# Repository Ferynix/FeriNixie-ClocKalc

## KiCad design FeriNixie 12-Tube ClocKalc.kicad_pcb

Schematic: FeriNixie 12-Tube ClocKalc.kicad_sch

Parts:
C1, C2, C3, C4, C5, C6, C7, C8, C9, C10, C11, C12, C51, C52: 100nF; C_1206_3216Metric; JLCPCB_PN C725802
C13, C14, C15, C16, C17, C18, C19, C20, C21, C22, C23, C24, C25, C26, C27, C28, C29, C30, C36: 1uF; C_0402_1005Metric; JLCPCB_PN C725802
C31, C32, C35, C37, C45, C46: 4.7uF; C_0402_1005Metric; JLCPCB_PN C725802
C33, C34: 15pF; C_0402_1005Metric; JLCPCB_PN C725802
C38, C39, C40, C41, C42, C43, C44, C47, C48: 100nF; C_0402_1005Metric; JLCPCB_PN C725802
D1: SMCJ150CA_C41411757; SMC_L6.9-W5.9-LS7.9-BI; LCSC C41411757
F1: C354900; C_Disc_D10.5mm_W5.0mm_P5.00mm; not fitted
J1: Conn_01x02_Socket; PinSocket_1x02_P1.00mm_Vertical
NE1: Run; NeonIndicator_A1B_A1C
NE2: NeonIndicator_2ML_1MH_B10A
NE3: Voltage Indicator; NeonIndicator_2ML_1MH_B10A
NE4: BLOWN; NeonIndicator_A1B_A1C
NX1, NX2, NX3, NX4, NX5, NX6, NX7, NX8, NX9, NX10, NX11, NX12: NixieTube_B-16851453_Burroughs
Q1, Q2, Q3, Q4, Q5, Q6, Q7, Q8, Q9, Q10, Q11, Q12, Q13, Q14, Q15, Q16, Q17, Q18, Q19, Q20, Q21, Q22, Q23, Q24, Q25, Q26, Q27, Q28, Q29, Q30, Q31, Q32, Q33, Q34, Q35, Q36, Q37, Q38, Q39, Q40, Q41, Q42, Q43, Q44, Q45, Q46, Q47, Q48, Q49, Q50, Q51, Q52, Q53, Q54, Q55, Q56, Q57, Q58, Q59, Q60, Q61, Q62, Q63, Q64, Q65, Q66, Q67, Q68, Q69, Q70, Q71, Q72, Q73, Q74, Q75, Q76, Q77, Q78, Q79, Q80, Q81, Q82, Q83, Q84, Q85, Q86, Q87, Q88, Q89, Q90, Q91, Q92, Q93, Q94, Q95, Q96, Q97, Q98, Q99, Q100, Q101, Q102, Q103, Q104, Q105, Q106, Q107, Q108, Q109, Q110, Q111, Q112, Q113, Q114, Q115, Q116, Q117, Q118, Q119, Q120, Q121, Q122, Q123, Q124, Q125, Q126, Q127, Q128, Q129, Q130, Q131, Q132, Q133, Q134, Q135, Q136, Q137, Q138, Q139, Q140, Q141, Q142, Q143, Q144: C22392287; SOT-23
R1, R2, R3, R4, R5, R6, R7, R8, R9, R10, R11, R12: 12K; R_1206_3216Metric
R13, R15, R16, R18, R19, R21, R22, R24, R25, R27, R28, R30, R31, R33, R34, R36, R37, R39, R40, R42, R43, R45, R46, R48: 56K; R_1206_3216Metric
R14, R17, R20, R23, R26, R29, R32, R35, R38, R41, R44, R47: 5.6K; R_1206_3216Metric
R49, R50, R51, R52, R53, R54, R55, R56, R57, R58, R59, R60, R61, R62, R63, R64, R65, R66, R67, R68, R69, R70, R71, R72, R73, R74, R75, R76, R77, R78, R79, R80, R81, R82, R83, R84, R85, R86, R87, R88, R89, R90, R91, R92, R93, R94, R95, R96, R97, R98, R99, R100, R101, R102, R103, R104, R105, R106, R107, R108, R109, R110, R111, R112, R113, R114, R115, R116, R117, R118, R119, R120, R121, R122, R123, R124, R125, R126, R127, R128, R129, R130, R131, R132, R133, R134, R135, R136, R137, R138, R139, R140, R141, R142, R143, R144, R145, R146, R147, R148, R149, R150, R151, R152, R153, R154, R155, R156, R157, R158, R159, R160, R161, R162, R163, R164, R165, R166, R167, R168, R169, R170, R171, R172, R173, R174, R175, R176, R177, R178, R179, R180, R181, R182, R183, R184, R185, R186, R187, R188, R189, R190, R191, R192, R197, R198, R199, R200, R201, R202, R203, R204, R205, R206, R207, R208, R209, R210, R211, R212, R213, R214, R215, R216, R217, R218, R219, R220, R221, R222, R223, R224, R225, R226, R227, R228, R229, R230, R231, R232, R233, R234, R235, R236, R237, R238, R239, R240, R241, R242, R243, R244, R245, R246, R247, R248, R249, R250, R251, R267, R269, R275, R276: 10K; R_0402_1005Metric
R193, R194, R195, R196: 560; R_0402_1005Metric
R252, R256, R264: 100K; R_1206_3216Metric
R254, R260: 5.1K; R_0402_1005Metric
R255, R262, R272: 200K; R_1206_3216Metric
R257, R258: 22; R_0402_1005Metric
R259: 4.7K; R_0402_1005Metric
R261: 1K; R_0402_1005Metric
R263: 22K; R_0402_1005Metric
R265: 200; R_0402_1005Metric
R266, R268, R270, R271, R273, R274, R277, R278: 100; R_0402_1005Metric
SW1: C309069; SW-TH_SS11-BBIWQ-XX; not fitted
U1, U2, U3, U4, U5, U6, U7, U8, U9, U10, U11, U12, U13, U14, U15, U16, U17, U18: 74HC595D,118; SOIC-16_L9.9-W3.9-P1.27-LS6.0-BL; LCSC C5947
U19, U20, U21, U22, U25: KT-0603R; LED-SMD_L1.6-W0.8-R-RD; LCSC C2286
U24: XC6206P332MR; SOT-23-3_L2.9-W1.3-P1.90-LS2.4-BR; LCSC C5446
U27: TYPE-C_16PIN_2MD(073); USB-C-SMD_TYPE-C-16PIN-2MD-073; LCSC C2765186
U28: RP2040; LQFN-56_L7.0-W7.0-P0.4-EP; LCSC C2040
U29, U30: TS-1187A-B-A-B; SW-SMD_4P-L5.1-W5.1-P3.70-LS6.5-TL_H1.5; LCSC C318884
U31: MB10S_C2488; MBS_L4.7-W3.8-P2.40-LS7.0-TL; LCSC C2488
U32: IRM-03-5; PWRM-TH_IRM-03-5-DIP5; LCSC C6969425; not fitted
U33: W25Q128JVSIQTR; SOIC-8_L5.3-W5.3-P1.27-LS8.0-BL; LCSC C97521
U34, U35, U36, U37, U38, U39, U40, U41: MMBTA42_C20069138; SOT-23-3_L2.9-W1.3-P1.90-LS2.4-BR; LCSC C20069138
X1: X322512MSB4SI; CRYSTAL-SMD_4P-L3.2-W2.5-BL; LCSC C9002

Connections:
+1V1: C46.1, C47.1, C48.1, U28.23 (DVDD), U28.45 (VREG_VOUT), U28.50 (DVDD)
+3V3: C31.2, C35.2, C38.1, C39.1, C40.1, C41.1, C42.1, C43.1, C44.1, C45.1, R265.1, U24.2 (Vout), U28.1 (IOVDD), U28.10 (IOVDD), U28.22 (IOVDD), U28.33 (IOVDD), U28.42 (IOVDD), U28.44 (VREG_IN), U28.48 (USB_VDD), U28.49 (IOVDD), U33.8 (VCC)
+5V: C13.1, C14.1, C15.1, C16.1, C17.1, C18.1, C19.1, C20.1, C21.1, C22.1, C23.1, C24.1, C25.1, C26.1, C27.1, C28.1, C29.1, C30.1, C32.2, C36.1, U1.16 (VCC), U2.16 (VCC), U3.16 (VCC), U4.16 (VCC), U5.16 (VCC), U6.16 (VCC), U7.16 (VCC), U8.16 (VCC), U9.16 (VCC), U10.16 (VCC), U11.16 (VCC), U12.16 (VCC), U13.16 (VCC), U14.16 (VCC), U15.16 (VCC), U16.16 (VCC), U17.16 (VCC), U18.16 (VCC), U24.3 (Vin), U25.1 (A), U27.A4B9 (VBUS), U27.B4A9 (VBUS), U32.16 (+VO)
+170V: C1.1, C2.1, C3.1, C4.1, C5.1, C6.1, C7.1, C8.1, C9.1, C10.1, C11.1, C12.1, C51.2, C52.2, D1.2, R1.2, R2.2, R3.2, R4.2, R5.2, R6.2, R7.2, R8.2, R9.2, R10.2, R11.2, R12.2, R252.1, R255.2, R256.1, R272.2, U31.1 (+)
/A_GPIO-26: U28.38 (GPIO26_ADC0)
/A_GPIO-27: U28.39 (GPIO27_ADC1)
/A_GPIO-28: U28.40 (GPIO28_ADC2)
/A_GPIO-29: U28.41 (GPIO29_ADC3)
/BOOT: R263.1, U28.56 (QSPI_SS), U33.1 (CS#)
/D+: R257.1, U28.47 (USB_DP)
/D-: R258.1, U28.46 (USB_DM)
/D_GPIO-0: R196.1, R197.1, R198.1, R199.1, R200.1, R201.1, R202.1, R203.1, R204.1, R205.1, R206.1, R207.1, R208.1, R209.1, R210.1, R211.1, R212.1, R213.1, R231.1, U28.2 (GPIO0)
/D_GPIO-1: R195.1, R214.1, R215.1, R216.1, R217.1, R218.1, R219.1, R220.1, R221.1, R222.1, R223.1, R224.1, R225.1, R226.1, R227.1, R228.1, R229.1, R230.1, R249.1, U28.3 (GPIO1)
/D_GPIO-2: R194.1, R232.1, R233.1, R234.1, R235.1, R236.1, R237.1, R238.1, R239.1, R240.1, R241.1, R242.1, R243.1, R244.1, R245.1, R246.1, R247.1, R248.1, R250.1, U28.4 (GPIO2)
/D_GPIO-3: R193.1, R251.1, U28.5 (GPIO3)
/D_GPIO-4: R275.2, R276.2, U28.6 (GPIO4)
/D_GPIO-5: R267.2, R269.2, U28.7 (GPIO5)
/D_GPIO-6: R266.2, R273.2, U28.8 (GPIO6)
/D_GPIO-7: U28.9 (GPIO7)
/D_GPIO-8: U28.11 (GPIO8)
/D_GPIO-9: U28.12 (GPIO9)
/D_GPIO-10: U28.13 (GPIO10)
/D_GPIO-11: U28.14 (GPIO11)
/D_GPIO-12: U28.15 (GPIO12)
/D_GPIO-13: U28.16 (GPIO13)
/D_GPIO-14: U28.17 (GPIO14)
/D_GPIO-15: U28.18 (GPIO15)
/D_GPIO-16: U28.27 (GPIO16)
/D_GPIO-17: U28.28 (GPIO17)
/D_GPIO-18: U28.29 (GPIO18)
/D_GPIO-19: U28.30 (GPIO19)
/D_GPIO-20: U28.31 (GPIO20)
/D_GPIO-21: U28.32 (GPIO21)
/D_GPIO-22: U28.34 (GPIO22)
/D_GPIO-23: U28.35 (GPIO23)
/D_GPIO-24: U28.36 (GPIO24)
/D_GPIO-25: U28.37 (GPIO25)
/FLIP_32kHz_0A: R274.2, R275.1, R277.1, U38.3 (C)
/FLIP_32kHz_0B: R267.1, R268.2, R270.1, U34.3 (C)
/FLIP_32kHz_1A: R276.1, R278.1, U39.3 (C)
/FLIP_32kHz_1B: R269.1, R271.1, U35.3 (C)
/MEM_CLK: U28.52 (QSPI_SCLK), U33.6 (CLK)
/MEM_DI: U28.53 (QSPI_SD0), U33.5 (DI)
/MEM_DO: U28.55 (QSPI_SD1), U33.2 (DO)
/XIN: C34.2, U28.20 (XIN), X1.1 (OSC1)
/XOUT: R261.1, U28.21 (XOUT)
/~MEM_HOLD: U28.51 (QSPI_SD3), U33.7 (IO3)
/~MEM_WP: U28.54 (QSPI_SD2), U33.3 (IO2)
/~RESET: U28.26 (RUN), U30.3 (C), U30.4 (D)
GND: C1.2, C2.2, C3.2, C4.2, C5.2, C6.2, C7.2, C8.2, C9.2, C10.2, C11.2, C12.2, C13.2, C14.2, C15.2, C16.2, C17.2, C18.2, C19.2, C20.2, C21.2, C22.2, C23.2, C24.2, C25.2, C26.2, C27.2, C28.2, C29.2, C30.2, C31.1, C32.1, C33.2, C34.1, C35.1, C36.2, C37.2, C38.2, C39.2, C40.2, C41.2, C42.2, C43.2, C44.2, C45.2, C46.2, C47.2, C48.2, C51.1, C52.1, D1.1, Q1.2 (E), Q2.2 (E), Q3.2 (E), Q4.2 (E), Q5.2 (E), Q6.2 (E), Q7.2 (E), Q8.2 (E), Q9.2 (E), Q10.2 (E), Q11.2 (E), Q12.2 (E), Q13.2 (E), Q14.2 (E), Q15.2 (E), Q16.2 (E), Q17.2 (E), Q18.2 (E), Q19.2 (E), Q20.2 (E), Q21.2 (E), Q22.2 (E), Q23.2 (E), Q24.2 (E), Q25.2 (E), Q26.2 (E), Q27.2 (E), Q28.2 (E), Q29.2 (E), Q30.2 (E), Q31.2 (E), Q32.2 (E), Q33.2 (E), Q34.2 (E), Q35.2 (E), Q36.2 (E), Q37.2 (E), Q38.2 (E), Q39.2 (E), Q40.2 (E), Q41.2 (E), Q42.2 (E), Q43.2 (E), Q44.2 (E), Q45.2 (E), Q46.2 (E), Q47.2 (E), Q48.2 (E), Q49.2 (E), Q50.2 (E), Q51.2 (E), Q52.2 (E), Q53.2 (E), Q54.2 (E), Q55.2 (E), Q56.2 (E), Q57.2 (E), Q58.2 (E), Q59.2 (E), Q60.2 (E), Q61.2 (E), Q62.2 (E), Q63.2 (E), Q64.2 (E), Q65.2 (E), Q66.2 (E), Q67.2 (E), Q68.2 (E), Q69.2 (E), Q70.2 (E), Q71.2 (E), Q72.2 (E), Q73.2 (E), Q74.2 (E), Q75.2 (E), Q76.2 (E), Q77.2 (E), Q78.2 (E), Q79.2 (E), Q80.2 (E), Q81.2 (E), Q82.2 (E), Q83.2 (E), Q84.2 (E), Q85.2 (E), Q86.2 (E), Q87.2 (E), Q88.2 (E), Q89.2 (E), Q90.2 (E), Q91.2 (E), Q92.2 (E), Q93.2 (E), Q94.2 (E), Q95.2 (E), Q96.2 (E), Q97.2 (E), Q98.2 (E), Q99.2 (E), Q100.2 (E), Q101.2 (E), Q102.2 (E), Q103.2 (E), Q104.2 (E), Q105.2 (E), Q106.2 (E), Q107.2 (E), Q108.2 (E), Q109.2 (E), Q110.2 (E), Q111.2 (E), Q112.2 (E), Q113.2 (E), Q114.2 (E), Q115.2 (E), Q116.2 (E), Q117.2 (E), Q118.2 (E), Q119.2 (E), Q120.2 (E), Q121.2 (E), Q122.2 (E), Q123.2 (E), Q124.2 (E), Q125.2 (E), Q126.2 (E), Q127.2 (E), Q128.2 (E), Q129.2 (E), Q130.2 (E), Q131.2 (E), Q132.2 (E), Q133.2 (E), Q134.2 (E), Q135.2 (E), Q136.2 (E), Q137.2 (E), Q138.2 (E), Q139.2 (E), Q140.2 (E), Q141.2 (E), Q142.2 (E), Q143.2 (E), Q144.2 (E), R254.1, R259.2, R260.1, U1.8 (GND), U1.13 (OE#), U2.8 (GND), U2.13 (OE#), U3.8 (GND), U3.13 (OE#), U4.8 (GND), U4.13 (OE#), U5.8 (GND), U5.13 (OE#), U6.8 (GND), U6.13 (OE#), U7.8 (GND), U7.13 (OE#), U8.8 (GND), U8.13 (OE#), U9.8 (GND), U9.13 (OE#), U10.8 (GND), U10.13 (OE#), U11.8 (GND), U11.13 (OE#), U12.8 (GND), U12.13 (OE#), U13.8 (GND), U13.13 (OE#), U14.8 (GND), U14.13 (OE#), U15.8 (GND), U15.13 (OE#), U16.8 (GND), U16.13 (OE#), U17.8 (GND), U17.13 (OE#), U18.8 (GND), U18.13 (OE#), U19.2 (K), U20.2 (K), U21.2 (K), U22.2 (K), U24.1 (GND), U27.13 (EH), U27.14 (EH), U27.A1B12 (GND), U27.B1A12 (GND), U28.19 (TESTEN), U28.57 (GND), U29.1 (A), U29.2 (B), U30.1 (A), U30.2 (B), U31.2 (-), U32.14 (-VO), U33.4 (GND), U34.2 (E), U35.2 (E), U36.2 (E), U37.2 (E), U38.2 (E), U39.2 (E), U40.2 (E), U41.2 (E), X1.2 (GND), X1.4 (GND)
unnamed: J1.1, U28.25 (SWD)
unnamed: J1.2, U28.24 (SWCLK)
unnamed: NE1.1 (A), R256.2, U41.3 (C)
unnamed: NE1.2 (K), R252.2, U40.3 (C)
unnamed: NE2.1 (A), R272.1, U37.3 (C)
unnamed: NE2.2 (K), R255.1, U36.3 (C)
unnamed: NE3.1 (A), R262.2
unnamed: NE4.1 (A), R264.2
unnamed: NX1.6 (0), Q5.3 (C)
unnamed: NX1.7 (1), R14.2
unnamed: NX1.8 (2), Q7.3 (C)
unnamed: NX1.9 (3), Q8.3 (C)
unnamed: NX1.10 (4), Q9.3 (C)
unnamed: NX1.12 (5), Q11.3 (C)
unnamed: NX1.13 (6), Q12.3 (C)
unnamed: NX1.2 (7), Q1.3 (C)
unnamed: NX1.3 (8), Q2.3 (C)
unnamed: NX1.5 (9), Q4.3 (C)
unnamed: NX1.1 (A), R1.1
unnamed: NX1.4 (LHDP), R13.2
unnamed: NX1.11 (RHDP), R15.2
unnamed: NX2.6 (0), Q17.3 (C)
unnamed: NX2.7 (1), R17.2
unnamed: NX2.8 (2), Q19.3 (C)
unnamed: NX2.9 (3), Q20.3 (C)
unnamed: NX2.10 (4), Q21.3 (C)
unnamed: NX2.12 (5), Q23.3 (C)
unnamed: NX2.13 (6), Q24.3 (C)
unnamed: NX2.2 (7), Q13.3 (C)
unnamed: NX2.3 (8), Q14.3 (C)
unnamed: NX2.5 (9), Q16.3 (C)
unnamed: NX2.1 (A), R2.1
unnamed: NX2.4 (LHDP), R16.2
unnamed: NX2.11 (RHDP), R18.2
unnamed: NX3.6 (0), Q29.3 (C)
unnamed: NX3.7 (1), R20.2
unnamed: NX3.8 (2), Q31.3 (C)
unnamed: NX3.9 (3), Q32.3 (C)
unnamed: NX3.10 (4), Q33.3 (C)
unnamed: NX3.12 (5), Q35.3 (C)
unnamed: NX3.13 (6), Q36.3 (C)
unnamed: NX3.2 (7), Q25.3 (C)
unnamed: NX3.3 (8), Q26.3 (C)
unnamed: NX3.5 (9), Q28.3 (C)
unnamed: NX3.1 (A), R3.1
unnamed: NX3.4 (LHDP), R19.2
unnamed: NX3.11 (RHDP), R21.2
unnamed: NX4.6 (0), Q41.3 (C)
unnamed: NX4.7 (1), R23.2
unnamed: NX4.8 (2), Q43.3 (C)
unnamed: NX4.9 (3), Q44.3 (C)
unnamed: NX4.10 (4), Q45.3 (C)
unnamed: NX4.12 (5), Q47.3 (C)
unnamed: NX4.13 (6), Q48.3 (C)
unnamed: NX4.2 (7), Q37.3 (C)
unnamed: NX4.3 (8), Q38.3 (C)
unnamed: NX4.5 (9), Q40.3 (C)
unnamed: NX4.1 (A), R4.1
unnamed: NX4.4 (LHDP), R22.2
unnamed: NX4.11 (RHDP), R24.2
unnamed: NX5.6 (0), Q53.3 (C)
unnamed: NX5.7 (1), R26.2
unnamed: NX5.8 (2), Q55.3 (C)
unnamed: NX5.9 (3), Q56.3 (C)
unnamed: NX5.10 (4), Q57.3 (C)
unnamed: NX5.12 (5), Q59.3 (C)
unnamed: NX5.13 (6), Q60.3 (C)
unnamed: NX5.2 (7), Q49.3 (C)
unnamed: NX5.3 (8), Q50.3 (C)
unnamed: NX5.5 (9), Q52.3 (C)
unnamed: NX5.1 (A), R5.1
unnamed: NX5.4 (LHDP), R25.2
unnamed: NX5.11 (RHDP), R27.2
unnamed: NX6.6 (0), Q65.3 (C)
unnamed: NX6.7 (1), R29.2
unnamed: NX6.8 (2), Q67.3 (C)
unnamed: NX6.9 (3), Q68.3 (C)
unnamed: NX6.10 (4), Q69.3 (C)
unnamed: NX6.12 (5), Q71.3 (C)
unnamed: NX6.13 (6), Q72.3 (C)
unnamed: NX6.2 (7), Q61.3 (C)
unnamed: NX6.3 (8), Q62.3 (C)
unnamed: NX6.5 (9), Q64.3 (C)
unnamed: NX6.1 (A), R6.1
unnamed: NX6.4 (LHDP), R28.2
unnamed: NX6.11 (RHDP), R30.2
unnamed: NX7.6 (0), Q77.3 (C)
unnamed: NX7.7 (1), R32.2
unnamed: NX7.8 (2), Q79.3 (C)
unnamed: NX7.9 (3), Q80.3 (C)
unnamed: NX7.10 (4), Q81.3 (C)
unnamed: NX7.12 (5), Q83.3 (C)
unnamed: NX7.13 (6), Q84.3 (C)
unnamed: NX7.2 (7), Q73.3 (C)
unnamed: NX7.3 (8), Q74.3 (C)
unnamed: NX7.5 (9), Q76.3 (C)
unnamed: NX7.1 (A), R7.1
unnamed: NX7.4 (LHDP), R31.2
unnamed: NX7.11 (RHDP), R33.2
unnamed: NX8.6 (0), Q89.3 (C)
unnamed: NX8.7 (1), R35.2
unnamed: NX8.8 (2), Q91.3 (C)
unnamed: NX8.9 (3), Q92.3 (C)
unnamed: NX8.10 (4), Q93.3 (C)
unnamed: NX8.12 (5), Q95.3 (C)
unnamed: NX8.13 (6), Q96.3 (C)
unnamed: NX8.2 (7), Q85.3 (C)
unnamed: NX8.3 (8), Q86.3 (C)
unnamed: NX8.5 (9), Q88.3 (C)
unnamed: NX8.1 (A), R8.1
unnamed: NX8.4 (LHDP), R34.2
unnamed: NX8.11 (RHDP), R36.2
unnamed: NX9.6 (0), Q101.3 (C)
unnamed: NX9.7 (1), R38.2
unnamed: NX9.8 (2), Q103.3 (C)
unnamed: NX9.9 (3), Q104.3 (C)
unnamed: NX9.10 (4), Q105.3 (C)
unnamed: NX9.12 (5), Q107.3 (C)
unnamed: NX9.13 (6), Q108.3 (C)
unnamed: NX9.2 (7), Q97.3 (C)
unnamed: NX9.3 (8), Q98.3 (C)
unnamed: NX9.5 (9), Q100.3 (C)
unnamed: NX9.1 (A), R9.1
unnamed: NX9.4 (LHDP), R37.2
unnamed: NX9.11 (RHDP), R39.2
unnamed: NX10.6 (0), Q113.3 (C)
unnamed: NX10.7 (1), R41.2
unnamed: NX10.8 (2), Q115.3 (C)
unnamed: NX10.9 (3), Q116.3 (C)
unnamed: NX10.10 (4), Q117.3 (C)
unnamed: NX10.12 (5), Q119.3 (C)
unnamed: NX10.13 (6), Q120.3 (C)
unnamed: NX10.2 (7), Q109.3 (C)
unnamed: NX10.3 (8), Q110.3 (C)
unnamed: NX10.5 (9), Q112.3 (C)
unnamed: NX10.1 (A), R10.1
unnamed: NX10.4 (LHDP), R40.2
unnamed: NX10.11 (RHDP), R42.2
unnamed: NX11.6 (0), Q125.3 (C)
unnamed: NX11.7 (1), R44.2
unnamed: NX11.8 (2), Q127.3 (C)
unnamed: NX11.9 (3), Q128.3 (C)
unnamed: NX11.10 (4), Q129.3 (C)
unnamed: NX11.12 (5), Q131.3 (C)
unnamed: NX11.13 (6), Q132.3 (C)
unnamed: NX11.2 (7), Q121.3 (C)
unnamed: NX11.3 (8), Q122.3 (C)
unnamed: NX11.5 (9), Q124.3 (C)
unnamed: NX11.1 (A), R11.1
unnamed: NX11.4 (LHDP), R43.2
unnamed: NX11.11 (RHDP), R45.2
unnamed: NX12.6 (0), Q137.3 (C)
unnamed: NX12.7 (1), R47.2
unnamed: NX12.8 (2), Q139.3 (C)
unnamed: NX12.9 (3), Q140.3 (C)
unnamed: NX12.10 (4), Q141.3 (C)
unnamed: NX12.12 (5), Q143.3 (C)
unnamed: NX12.13 (6), Q144.3 (C)
unnamed: NX12.2 (7), Q133.3 (C)
unnamed: NX12.3 (8), Q134.3 (C)
unnamed: NX12.5 (9), Q136.3 (C)
unnamed: NX12.1 (A), R12.1
unnamed: NX12.4 (LHDP), R46.2
unnamed: NX12.11 (RHDP), R48.2
unnamed: Q1.1 (B), R49.2
unnamed: Q2.1 (B), R50.2
unnamed: Q3.1 (B), R51.2
unnamed: Q3.3 (C), R13.1
unnamed: Q4.1 (B), R52.2
unnamed: Q5.1 (B), R53.2
unnamed: Q6.1 (B), R54.2
unnamed: Q6.3 (C), R14.1
unnamed: Q7.1 (B), R55.2
unnamed: Q8.1 (B), R56.2
unnamed: Q9.1 (B), R57.2
unnamed: Q10.1 (B), R58.2
unnamed: Q10.3 (C), R15.1
unnamed: Q11.1 (B), R59.2
unnamed: Q12.1 (B), R60.2
unnamed: Q13.1 (B), R61.2
unnamed: Q14.1 (B), R62.2
unnamed: Q15.1 (B), R63.2
unnamed: Q15.3 (C), R16.1
unnamed: Q16.1 (B), R64.2
unnamed: Q17.1 (B), R65.2
unnamed: Q18.1 (B), R66.2
unnamed: Q18.3 (C), R17.1
unnamed: Q19.1 (B), R67.2
unnamed: Q20.1 (B), R68.2
unnamed: Q21.1 (B), R69.2
unnamed: Q22.1 (B), R70.2
unnamed: Q22.3 (C), R18.1
unnamed: Q23.1 (B), R71.2
unnamed: Q24.1 (B), R72.2
unnamed: Q25.1 (B), R73.2
unnamed: Q26.1 (B), R74.2
unnamed: Q27.1 (B), R75.2
unnamed: Q27.3 (C), R19.1
unnamed: Q28.1 (B), R76.2
unnamed: Q29.1 (B), R77.2
unnamed: Q30.1 (B), R78.2
unnamed: Q30.3 (C), R20.1
unnamed: Q31.1 (B), R79.2
unnamed: Q32.1 (B), R80.2
unnamed: Q33.1 (B), R81.2
unnamed: Q34.1 (B), R82.2
unnamed: Q34.3 (C), R21.1
unnamed: Q35.1 (B), R83.2
unnamed: Q36.1 (B), R84.2
unnamed: Q37.1 (B), R85.2
unnamed: Q38.1 (B), R86.2
unnamed: Q39.1 (B), R87.2
unnamed: Q39.3 (C), R22.1
unnamed: Q40.1 (B), R88.2
unnamed: Q41.1 (B), R89.2
unnamed: Q42.1 (B), R90.2
unnamed: Q42.3 (C), R23.1
unnamed: Q43.1 (B), R91.2
unnamed: Q44.1 (B), R92.2
unnamed: Q45.1 (B), R93.2
unnamed: Q46.1 (B), R94.2
unnamed: Q46.3 (C), R24.1
unnamed: Q47.1 (B), R95.2
unnamed: Q48.1 (B), R96.2
unnamed: Q49.1 (B), R97.2
unnamed: Q50.1 (B), R98.2
unnamed: Q51.1 (B), R99.2
unnamed: Q51.3 (C), R25.1
unnamed: Q52.1 (B), R100.2
unnamed: Q53.1 (B), R101.2
unnamed: Q54.1 (B), R102.2
unnamed: Q54.3 (C), R26.1
unnamed: Q55.1 (B), R103.2
unnamed: Q56.1 (B), R104.2
unnamed: Q57.1 (B), R105.2
unnamed: Q58.1 (B), R106.2
unnamed: Q58.3 (C), R27.1
unnamed: Q59.1 (B), R107.2
unnamed: Q60.1 (B), R108.2
unnamed: Q61.1 (B), R109.2
unnamed: Q62.1 (B), R110.2
unnamed: Q63.1 (B), R111.2
unnamed: Q63.3 (C), R28.1
unnamed: Q64.1 (B), R112.2
unnamed: Q65.1 (B), R113.2
unnamed: Q66.1 (B), R114.2
unnamed: Q66.3 (C), R29.1
unnamed: Q67.1 (B), R115.2
unnamed: Q68.1 (B), R116.2
unnamed: Q69.1 (B), R117.2
unnamed: Q70.1 (B), R118.2
unnamed: Q70.3 (C), R30.1
unnamed: Q71.1 (B), R119.2
unnamed: Q72.1 (B), R120.2
unnamed: Q73.1 (B), R121.2
unnamed: Q74.1 (B), R122.2
unnamed: Q75.1 (B), R123.2
unnamed: Q75.3 (C), R31.1
unnamed: Q76.1 (B), R124.2
unnamed: Q77.1 (B), R125.2
unnamed: Q78.1 (B), R126.2
unnamed: Q78.3 (C), R32.1
unnamed: Q79.1 (B), R127.2
unnamed: Q80.1 (B), R128.2
unnamed: Q81.1 (B), R129.2
unnamed: Q82.1 (B), R130.2
unnamed: Q82.3 (C), R33.1
unnamed: Q83.1 (B), R131.2
unnamed: Q84.1 (B), R132.2
unnamed: Q85.1 (B), R133.2
unnamed: Q86.1 (B), R134.2
unnamed: Q87.1 (B), R135.2
unnamed: Q87.3 (C), R34.1
unnamed: Q88.1 (B), R136.2
unnamed: Q89.1 (B), R137.2
unnamed: Q90.1 (B), R138.2
unnamed: Q90.3 (C), R35.1
unnamed: Q91.1 (B), R139.2
unnamed: Q92.1 (B), R140.2
unnamed: Q93.1 (B), R141.2
unnamed: Q94.1 (B), R142.2
unnamed: Q94.3 (C), R36.1
unnamed: Q95.1 (B), R143.2
unnamed: Q96.1 (B), R144.2
unnamed: Q97.1 (B), R145.2
unnamed: Q98.1 (B), R146.2
unnamed: Q99.1 (B), R147.2
unnamed: Q99.3 (C), R37.1
unnamed: Q100.1 (B), R148.2
unnamed: Q101.1 (B), R149.2
unnamed: Q102.1 (B), R150.2
unnamed: Q102.3 (C), R38.1
unnamed: Q103.1 (B), R151.2
unnamed: Q104.1 (B), R152.2
unnamed: Q105.1 (B), R153.2
unnamed: Q106.1 (B), R154.2
unnamed: Q106.3 (C), R39.1
unnamed: Q107.1 (B), R155.2
unnamed: Q108.1 (B), R156.2
unnamed: Q109.1 (B), R157.2
unnamed: Q110.1 (B), R158.2
unnamed: Q111.1 (B), R159.2
unnamed: Q111.3 (C), R40.1
unnamed: Q112.1 (B), R160.2
unnamed: Q113.1 (B), R161.2
unnamed: Q114.1 (B), R162.2
unnamed: Q114.3 (C), R41.1
unnamed: Q115.1 (B), R163.2
unnamed: Q116.1 (B), R164.2
unnamed: Q117.1 (B), R165.2
unnamed: Q118.1 (B), R166.2
unnamed: Q118.3 (C), R42.1
unnamed: Q119.1 (B), R167.2
unnamed: Q120.1 (B), R168.2
unnamed: Q121.1 (B), R169.2
unnamed: Q122.1 (B), R170.2
unnamed: Q123.1 (B), R171.2
unnamed: Q123.3 (C), R43.1
unnamed: Q124.1 (B), R172.2
unnamed: Q125.1 (B), R173.2
unnamed: Q126.1 (B), R174.2
unnamed: Q126.3 (C), R44.1
unnamed: Q127.1 (B), R175.2
unnamed: Q128.1 (B), R176.2
unnamed: Q129.1 (B), R177.2
unnamed: Q130.1 (B), R178.2
unnamed: Q130.3 (C), R45.1
unnamed: Q131.1 (B), R179.2
unnamed: Q132.1 (B), R180.2
unnamed: Q133.1 (B), R181.2
unnamed: Q134.1 (B), R182.2
unnamed: Q135.1 (B), R183.2
unnamed: Q135.3 (C), R46.1
unnamed: Q136.1 (B), R184.2
unnamed: Q137.1 (B), R185.2
unnamed: Q138.1 (B), R186.2
unnamed: Q138.3 (C), R47.1
unnamed: Q139.1 (B), R187.2
unnamed: Q140.1 (B), R188.2
unnamed: Q141.1 (B), R189.2
unnamed: Q142.1 (B), R190.2
unnamed: Q142.3 (C), R48.1
unnamed: Q143.1 (B), R191.2
unnamed: Q144.1 (B), R192.2
unnamed: F1.1, R264.1, SW1.1 (A)
unnamed: R251.2, U1.14 (DS)
unnamed: R205.2, U1.10 (MR#)
unnamed: R49.1, U1.15 (Q0)
unnamed: R50.1, U1.1 (Q1)
unnamed: R51.1, U1.2 (Q2)
unnamed: R52.1, U1.3 (Q3)
unnamed: R53.1, U1.4 (Q4)
unnamed: R54.1, U1.5 (Q5)
unnamed: R55.1, U1.6 (Q6)
unnamed: R56.1, U1.7 (Q7)
unnamed: U1.9 (Q7S), U2.14 (DS)
unnamed: R222.2, U1.11 (SHCP)
unnamed: R240.2, U1.12 (STCP)
unnamed: R210.2, U2.10 (MR#)
unnamed: R57.1, U2.15 (Q0)
unnamed: R58.1, U2.1 (Q1)
unnamed: R59.1, U2.2 (Q2)
unnamed: R60.1, U2.3 (Q3)
unnamed: R61.1, U2.4 (Q4)
unnamed: R62.1, U2.5 (Q5)
unnamed: R63.1, U2.6 (Q6)
unnamed: R64.1, U2.7 (Q7)
unnamed: U2.9 (Q7S), U3.14 (DS)
unnamed: R227.2, U2.11 (SHCP)
unnamed: R245.2, U2.12 (STCP)
unnamed: R203.2, U3.10 (MR#)
unnamed: R65.1, U3.15 (Q0)
unnamed: R66.1, U3.1 (Q1)
unnamed: R67.1, U3.2 (Q2)
unnamed: R68.1, U3.3 (Q3)
unnamed: R69.1, U3.4 (Q4)
unnamed: R70.1, U3.5 (Q5)
unnamed: R71.1, U3.6 (Q6)
unnamed: R72.1, U3.7 (Q7)
unnamed: U3.9 (Q7S), U4.14 (DS)
unnamed: R220.2, U3.11 (SHCP)
unnamed: R238.2, U3.12 (STCP)
unnamed: R206.2, U4.10 (MR#)
unnamed: R73.1, U4.15 (Q0)
unnamed: R74.1, U4.1 (Q1)
unnamed: R75.1, U4.2 (Q2)
unnamed: R76.1, U4.3 (Q3)
unnamed: R77.1, U4.4 (Q4)
unnamed: R78.1, U4.5 (Q5)
unnamed: R79.1, U4.6 (Q6)
unnamed: R80.1, U4.7 (Q7)
unnamed: U4.9 (Q7S), U5.14 (DS)
unnamed: R223.2, U4.11 (SHCP)
unnamed: R241.2, U4.12 (STCP)
unnamed: R204.2, U5.10 (MR#)
unnamed: R81.1, U5.15 (Q0)
unnamed: R82.1, U5.1 (Q1)
unnamed: R83.1, U5.2 (Q2)
unnamed: R84.1, U5.3 (Q3)
unnamed: R85.1, U5.4 (Q4)
unnamed: R86.1, U5.5 (Q5)
unnamed: R87.1, U5.6 (Q6)
unnamed: R88.1, U5.7 (Q7)
unnamed: U5.9 (Q7S), U6.14 (DS)
unnamed: R221.2, U5.11 (SHCP)
unnamed: R239.2, U5.12 (STCP)
unnamed: R207.2, U6.10 (MR#)
unnamed: R89.1, U6.15 (Q0)
unnamed: R90.1, U6.1 (Q1)
unnamed: R91.1, U6.2 (Q2)
unnamed: R92.1, U6.3 (Q3)
unnamed: R93.1, U6.4 (Q4)
unnamed: R94.1, U6.5 (Q5)
unnamed: R95.1, U6.6 (Q6)
unnamed: R96.1, U6.7 (Q7)
unnamed: U6.9 (Q7S), U7.14 (DS)
unnamed: R224.2, U6.11 (SHCP)
unnamed: R242.2, U6.12 (STCP)
unnamed: R211.2, U7.10 (MR#)
unnamed: R97.1, U7.15 (Q0)
unnamed: R98.1, U7.1 (Q1)
unnamed: R99.1, U7.2 (Q2)
unnamed: R100.1, U7.3 (Q3)
unnamed: R101.1, U7.4 (Q4)
unnamed: R102.1, U7.5 (Q5)
unnamed: R103.1, U7.6 (Q6)
unnamed: R104.1, U7.7 (Q7)
unnamed: U7.9 (Q7S), U8.14 (DS)
unnamed: R228.2, U7.11 (SHCP)
unnamed: R246.2, U7.12 (STCP)
unnamed: R213.2, U8.10 (MR#)
unnamed: R105.1, U8.15 (Q0)
unnamed: R106.1, U8.1 (Q1)
unnamed: R107.1, U8.2 (Q2)
unnamed: R108.1, U8.3 (Q3)
unnamed: R109.1, U8.4 (Q4)
unnamed: R110.1, U8.5 (Q5)
unnamed: R111.1, U8.6 (Q6)
unnamed: R112.1, U8.7 (Q7)
unnamed: U8.9 (Q7S), U9.14 (DS)
unnamed: R230.2, U8.11 (SHCP)
unnamed: R248.2, U8.12 (STCP)
unnamed: R208.2, U9.10 (MR#)
unnamed: R113.1, U9.15 (Q0)
unnamed: R114.1, U9.1 (Q1)
unnamed: R115.1, U9.2 (Q2)
unnamed: R116.1, U9.3 (Q3)
unnamed: R117.1, U9.4 (Q4)
unnamed: R118.1, U9.5 (Q5)
unnamed: R119.1, U9.6 (Q6)
unnamed: R120.1, U9.7 (Q7)
unnamed: R225.2, U9.11 (SHCP)
unnamed: R243.2, U9.12 (STCP)
unnamed: U9.9 (Q7S), U10.14 (DS)
unnamed: R212.2, U10.10 (MR#)
unnamed: R121.1, U10.15 (Q0)
unnamed: R122.1, U10.1 (Q1)
unnamed: R123.1, U10.2 (Q2)
unnamed: R124.1, U10.3 (Q3)
unnamed: R125.1, U10.4 (Q4)
unnamed: R126.1, U10.5 (Q5)
unnamed: R127.1, U10.6 (Q6)
unnamed: R128.1, U10.7 (Q7)
unnamed: U10.9 (Q7S), U11.14 (DS)
unnamed: R229.2, U10.11 (SHCP)
unnamed: R247.2, U10.12 (STCP)
unnamed: R209.2, U11.10 (MR#)
unnamed: R129.1, U11.15 (Q0)
unnamed: R130.1, U11.1 (Q1)
unnamed: R131.1, U11.2 (Q2)
unnamed: R132.1, U11.3 (Q3)
unnamed: R133.1, U11.4 (Q4)
unnamed: R134.1, U11.5 (Q5)
unnamed: R135.1, U11.6 (Q6)
unnamed: R136.1, U11.7 (Q7)
unnamed: U11.9 (Q7S), U12.14 (DS)
unnamed: R226.2, U11.11 (SHCP)
unnamed: R244.2, U11.12 (STCP)
unnamed: R201.2, U12.10 (MR#)
unnamed: R137.1, U12.15 (Q0)
unnamed: R138.1, U12.1 (Q1)
unnamed: R139.1, U12.2 (Q2)
unnamed: R140.1, U12.3 (Q3)
unnamed: R141.1, U12.4 (Q4)
unnamed: R142.1, U12.5 (Q5)
unnamed: R143.1, U12.6 (Q6)
unnamed: R144.1, U12.7 (Q7)
unnamed: U12.9 (Q7S), U13.14 (DS)
unnamed: R218.2, U12.11 (SHCP)
unnamed: R236.2, U12.12 (STCP)
unnamed: R199.2, U13.10 (MR#)
unnamed: R145.1, U13.15 (Q0)
unnamed: R146.1, U13.1 (Q1)
unnamed: R147.1, U13.2 (Q2)
unnamed: R148.1, U13.3 (Q3)
unnamed: R149.1, U13.4 (Q4)
unnamed: R150.1, U13.5 (Q5)
unnamed: R151.1, U13.6 (Q6)
unnamed: R152.1, U13.7 (Q7)
unnamed: U13.9 (Q7S), U14.14 (DS)
unnamed: R216.2, U13.11 (SHCP)
unnamed: R234.2, U13.12 (STCP)
unnamed: R202.2, U14.10 (MR#)
unnamed: R153.1, U14.15 (Q0)
unnamed: R154.1, U14.1 (Q1)
unnamed: R155.1, U14.2 (Q2)
unnamed: R156.1, U14.3 (Q3)
unnamed: R157.1, U14.4 (Q4)
unnamed: R158.1, U14.5 (Q5)
unnamed: R159.1, U14.6 (Q6)
unnamed: R160.1, U14.7 (Q7)
unnamed: U14.9 (Q7S), U15.14 (DS)
unnamed: R219.2, U14.11 (SHCP)
unnamed: R237.2, U14.12 (STCP)
unnamed: R197.2, U15.10 (MR#)
unnamed: R161.1, U15.15 (Q0)
unnamed: R162.1, U15.1 (Q1)
unnamed: R163.1, U15.2 (Q2)
unnamed: R164.1, U15.3 (Q3)
unnamed: R165.1, U15.4 (Q4)
unnamed: R166.1, U15.5 (Q5)
unnamed: R167.1, U15.6 (Q6)
unnamed: R168.1, U15.7 (Q7)
unnamed: U15.9 (Q7S), U16.14 (DS)
unnamed: R214.2, U15.11 (SHCP)
unnamed: R232.2, U15.12 (STCP)
unnamed: R200.2, U16.10 (MR#)
unnamed: R169.1, U16.15 (Q0)
unnamed: R170.1, U16.1 (Q1)
unnamed: R171.1, U16.2 (Q2)
unnamed: R172.1, U16.3 (Q3)
unnamed: R173.1, U16.4 (Q4)
unnamed: R174.1, U16.5 (Q5)
unnamed: R175.1, U16.6 (Q6)
unnamed: R176.1, U16.7 (Q7)
unnamed: U16.9 (Q7S), U17.14 (DS)
unnamed: R217.2, U16.11 (SHCP)
unnamed: R235.2, U16.12 (STCP)
unnamed: R198.2, U17.10 (MR#)
unnamed: R177.1, U17.15 (Q0)
unnamed: R178.1, U17.1 (Q1)
unnamed: R179.1, U17.2 (Q2)
unnamed: R180.1, U17.3 (Q3)
unnamed: R181.1, U17.4 (Q4)
unnamed: R182.1, U17.5 (Q5)
unnamed: R183.1, U17.6 (Q6)
unnamed: R184.1, U17.7 (Q7)
unnamed: U17.9 (Q7S), U18.14 (DS)
unnamed: R215.2, U17.11 (SHCP)
unnamed: R233.2, U17.12 (STCP)
unnamed: R231.2, U18.10 (MR#)
unnamed: R185.1, U18.15 (Q0)
unnamed: R186.1, U18.1 (Q1)
unnamed: R187.1, U18.2 (Q2)
unnamed: R188.1, U18.3 (Q3)
unnamed: R189.1, U18.4 (Q4)
unnamed: R190.1, U18.5 (Q5)
unnamed: R191.1, U18.6 (Q6)
unnamed: R192.1, U18.7 (Q7)
unnamed: R249.2, U18.11 (SHCP)
unnamed: R250.2, U18.12 (STCP)
unnamed: R193.2, U19.1 (A)
unnamed: R194.2, U20.1 (A)
unnamed: R195.2, U21.1 (A)
unnamed: R196.2, U22.1 (A)
unnamed: R259.1, U25.2 (K)
unnamed: R254.2, U27.A5 (CC1)
unnamed: R260.2, U27.B5 (CC2)
unnamed: R258.2, U27.A7 (Dn1), U27.B7 (Dn2)
unnamed: R257.2, U27.A6 (Dp1), U27.B6 (Dp2)
unnamed: C37.1, R265.2, U28.43 (ADC_AVDD)
unnamed: R263.2, U29.3 (C), U29.4 (D)
unnamed: R266.1, U34.1 (B)
unnamed: R268.1, U35.1 (B)
unnamed: R270.2, U36.1 (B)
unnamed: R271.2, U37.1 (B)
unnamed: R273.1, U38.1 (B)
unnamed: R274.1, U39.1 (B)
unnamed: R277.2, U40.1 (B)
unnamed: R278.2, U41.1 (B)
unnamed: C33.1, R261.2, X1.3 (OSC2)
POW: F1.2, NE4.2 (K), U31.3 (C2), U32.1 (AC/L)
VAC: R262.1, SW1.2 (B)
VCOM: NE3.2 (K), U31.4 (C1), U32.3 (AC/N)

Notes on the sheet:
~{Reset}
Serial Clock
Latch Clock
Serial

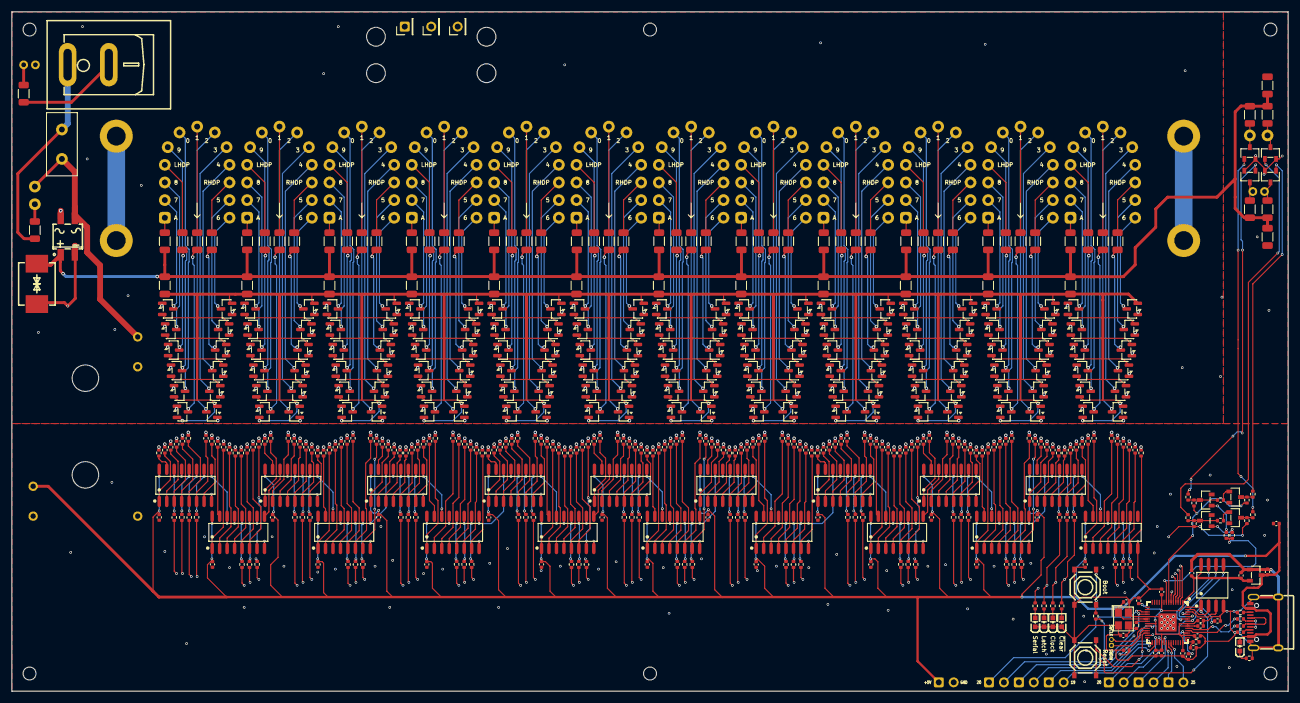
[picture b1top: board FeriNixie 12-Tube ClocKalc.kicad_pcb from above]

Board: 4 copper layers, 217.0 x 115.5 mm, 531 parts (1 on the bottom side), 611 nets.

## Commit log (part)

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2026-06-21 Tooooons of changes... stupid amount of changes
2026-06-27 Finalize changes for printing
2026-06-27 Final changes before printing
